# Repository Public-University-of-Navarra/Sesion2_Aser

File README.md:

# Sesión 2 · Arquitectura base

Desarrollo de Equipos Electrónicos · Máster UPNA · Aser Méndez

Placa mínima: entrada de 9 V por bornas → LDO de 3,3 V → microcontrolador STM32G031K8T6 con tres entradas analógicas filtradas (RC paso bajo 1 kΩ / 100 nF, fc ≈ 1,6 kHz), una salida digital y conector SWD.

## Estructura
- Sesion2_Aser.kicad_sch (raíz): J101 (bornas 9 V) y los bloques Alimentacion y Microcontrolador.
- Alimentacion.kicad_sch: U201 MCP1703A-3302E/DB con C201 y C202.
- Microcontrolador.kicad_sch: U301 STM32G031K8T6, J301 (E/S), J302 (SWD), C301 y tres instancias de FiltroRC.kicad_sch.
- Tensiones por pines jerárquicos: VIN (raíz → Alimentacion) y 3V3 (Alimentacion → Microcontrolador). GND común.

## Selección de componentes (Mouser)
| Función | MPN | Fabricante | Motivo |
|---|---|---|---|
| MCU | STM32G031K8T6 | STMicroelectronics | Cortex-M0+, 1,7–3,6 V, LQFP-32, activo |
| LDO 3,3 V | MCP1703A-3302E/DB | Microchip | Hasta 16 V de entrada (9 V con margen), 250 mA, cerámicos de 1 µF |
| Bornas alimentación | 1715721 | Phoenix Contact | 2 polos, paso 5,08 mm |
| Conector SWD | 61300511121 | Würth Elektronik | Tira 1×5, 2,54 mm |
| Conector E/S | 61300611121 | Würth Elektronik | Tira 1×6, 2,54 mm |

## Ramas
- main: estructura e integración
- alimentacion: hoja de alimentación
- microcontrolador: hoja del MCU y BOM

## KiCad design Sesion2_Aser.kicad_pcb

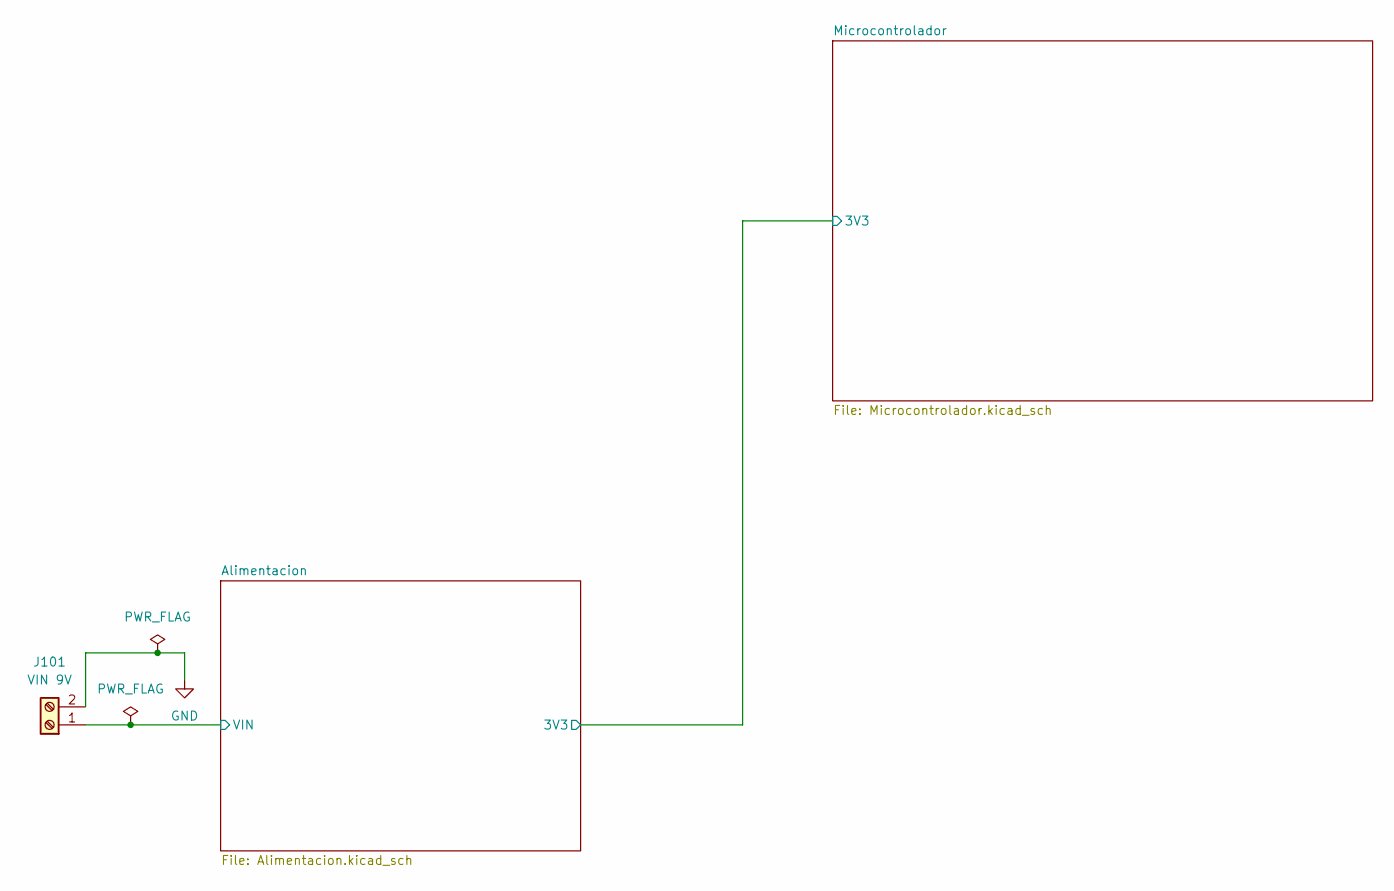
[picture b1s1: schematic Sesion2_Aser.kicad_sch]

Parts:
J101: VIN 9V; TerminalBlock_Phoenix_MKDS-1,5-2-5.08_1x02_P5.08mm_Horizont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; MPN 1715721

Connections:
/Alimentacion/VIN: J101.1; also elsewhere on the board
GND: J101.2; also elsewhere on the board

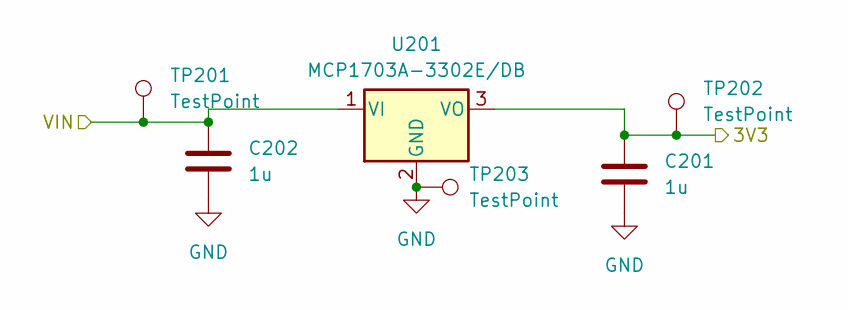
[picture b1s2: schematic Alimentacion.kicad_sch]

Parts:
C201, C202: 1u; C_0805_2012Metric_Pad1.18x1.45mm_HandSolder; MPN GRM21BR71H105KA12L
TP201, TP202: TestPoint; TestPoint_Keystone_5000-5004_Miniature; MPN 5000
TP203: TestPoint; TestPoint_Keystone_5000-5004_Miniature; MPN 5001
U201: MCP1703A-3302E/DB; SOT-223-3_TabPin2; MPN MCP1703A-3302E/DB

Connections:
/Alimentacion/3V3: C201.1, TP202.1 (1_1), U201.3 (VO); also elsewhere on the board
/Alimentacion/VIN: C202.1, TP201.1 (1_1), U201.1 (VI); also elsewhere on the board
GND: C201.2, C202.2, TP203.1 (1_1), U201.2 (GND); also elsewhere on the board

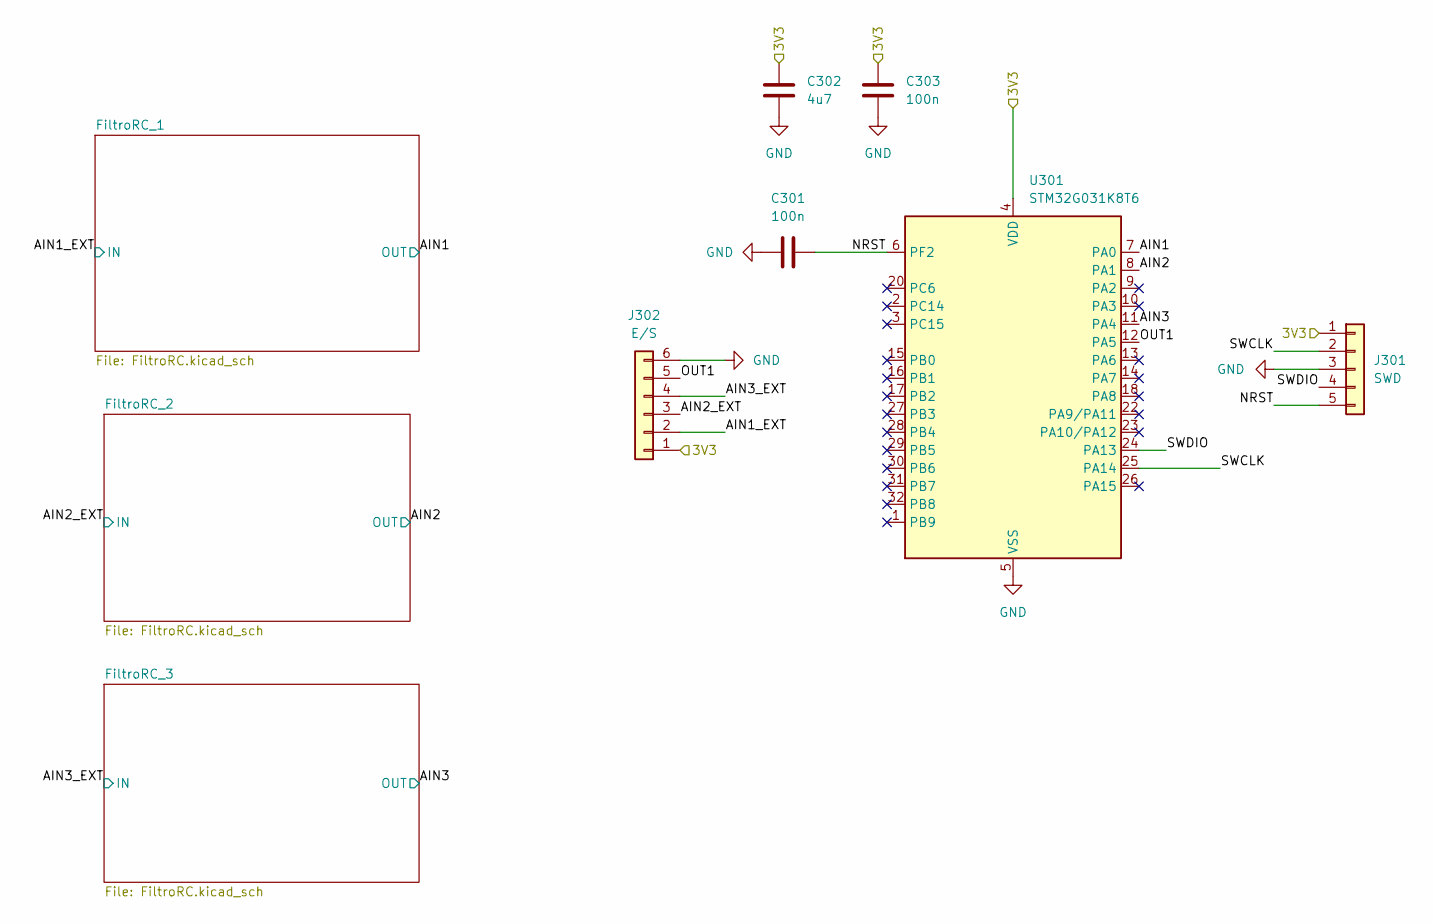
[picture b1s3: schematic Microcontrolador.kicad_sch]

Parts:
C301, C303: 100n; C_0805_2012Metric_Pad1.18x1.45mm_HandSolder; MPN CC0805KRX7R9BB104
C302: 4u7; C_0805_2012Metric_Pad1.18x1.45mm_HandSolder; MPN GRM21BR71E475KA73L
J301: SWD; PinHeader_1x05_P2.54mm_Vertical; MPN 61300511121
J302: E/S; PinHeader_1x06_P2.54mm_Vertical; MPN 61300611121
U301: STM32G031K8T6; LQFP-32_7x7mm_P0.8mm; MPN STM32G031K8T6

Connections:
/Alimentacion/3V3: C302.1, C303.1, J301.1, J302.1, U301.4 (VDD); also elsewhere on the board
/Microcontrolador/AIN1: U301.7 (PA0); also elsewhere on the board
/Microcontrolador/AIN1_EXT: J302.2; also elsewhere on the board
/Microcontrolador/AIN2: U301.8 (PA1); also elsewhere on the board
/Microcontrolador/AIN2_EXT: J302.3; also elsewhere on the board
/Microcontrolador/AIN3: U301.11 (PA4); also elsewhere on the board
/Microcontrolador/AIN3_EXT: J302.4; also elsewhere on the board
/Microcontrolador/NRST: C301.2, J301.5, U301.6 (PF2)
/Microcontrolador/OUT1: J302.5, U301.12 (PA5)
/Microcontrolador/SWCLK: J301.2, U301.25 (PA14)
/Microcontrolador/SWDIO: J301.4, U301.24 (PA13)
GND: C301.1, C302.2, C303.2, J301.3, J302.6, U301.5 (VSS); also elsewhere on the board

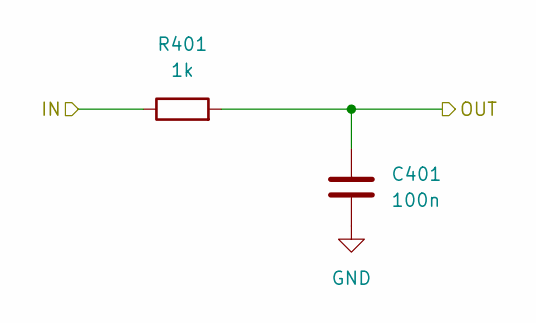
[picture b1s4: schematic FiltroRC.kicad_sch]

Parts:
C401: 100n; C_0805_2012Metric_Pad1.18x1.45mm_HandSolder; MPN CC0805KRX7R9BB104
R401: 1k; R_0805_2012Metric_Pad1.20x1.40mm_HandSolder; MPN RC0805FR-071KL

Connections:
/Microcontrolador/AIN1: C401.2, R401.2; also elsewhere on the board
/Microcontrolador/AIN1_EXT: R401.1; also elsewhere on the board
GND: C401.1; also elsewhere on the board

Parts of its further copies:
C501, C601: 100n; C_0805_2012Metric_Pad1.18x1.45mm_HandSolder; MPN CC0805KRX7R9BB104
R501, R601: 1k; R_0805_2012Metric_Pad1.20x1.40mm_HandSolder; MPN RC0805FR-071KL

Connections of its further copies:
/Microcontrolador/AIN2: C501.2, R501.2; also elsewhere on the board
/Microcontrolador/AIN2_EXT: R501.1; also elsewhere on the board
/Microcontrolador/AIN3: C601.2, R601.2; also elsewhere on the board
/Microcontrolador/AIN3_EXT: R601.1; also elsewhere on the board
GND: C501.1, C601.1; also elsewhere on the board

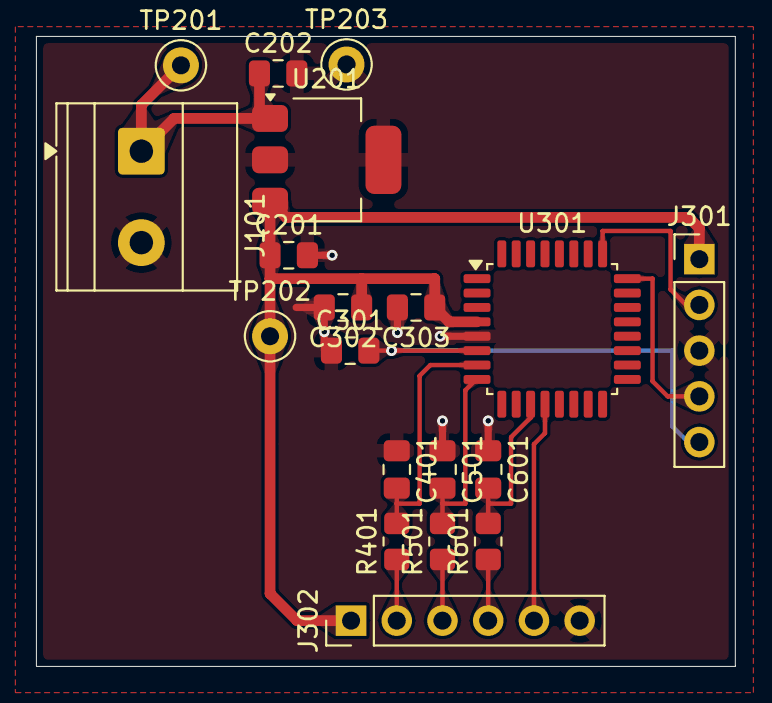
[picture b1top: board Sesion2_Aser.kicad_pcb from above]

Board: 2 copper layers, 38.8 x 35.0 mm, 19 parts (0 on the bottom side), 13 nets.
